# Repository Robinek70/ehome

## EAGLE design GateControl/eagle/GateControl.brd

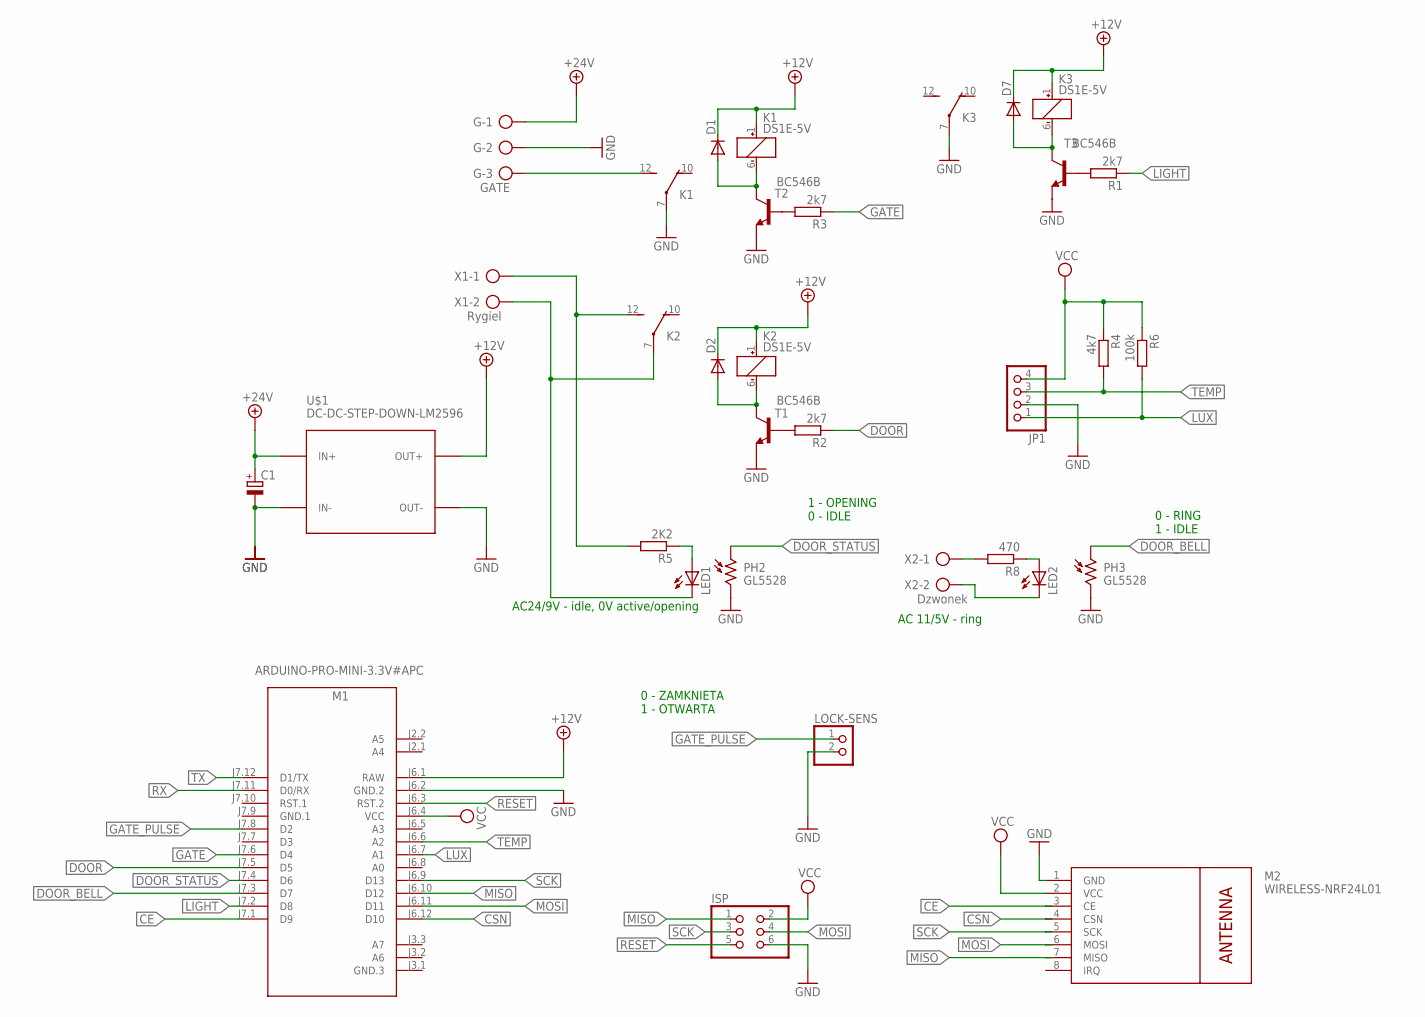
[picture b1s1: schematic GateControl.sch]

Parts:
C1: CPOL-EUE3.5-10; E3,5-10
D1, D2, D7: DIODE-C1702-05; C1702-05
G: GATE; AK500/3
ISP: PINHD-2X03_2.54; 2X03
JP1: PINHD-1X04_2.54; 1X04
K1, K2, K3: DS1E-5V; DS1E
LED1, LED2: LED5MM
LOCK-SENS: PINHD-1X02_2.54; 1X02
M1: ARDUINO-PRO-MINI-3.3V#APC; ARDUINO-PRO-MINI#APC
M2: WIRELESS-NRF24L01
PH2, PH3: GL5528; TO46-VT200
R1, R2, R3: 2k7; 0309V
R4: 4k7; 0309V
R5: 2K2; 0309V
R6: 100k; 0309V
R8: 470; 0309V
T1, T2, T3: BC546B; TO92-EBC
U$1: DC-DC-STEP-DOWN-LM2596
X1: Rygiel; AK500/2
X2: Dzwonek; AK500/2

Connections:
+12V: D1.C, D2.C, D7.C, K1.1 (+), K2.1 (+), K3.1 (+), M1.J6.1 (RAW), U$1.OUT+
+24V: C1.+, G.1, U$1.IN+
CE: M1.J7.1 (D9), M2.3 (CE)
CSN: M1.J6.12 (D10), M2.4 (CSN)
DOOR: M1.J7.5 (D5), R2.1
DOOR_BELL: M1.J7.3 (D7), PH3.1
DOOR_STATUS: M1.J7.4 (D6), PH2.1
GATE: M1.J7.6 (D4), R3.1
GATE_PULSE: LOCK-SENS.1, M1.J7.8 (D2)
GND: C1.-, G.2, ISP.6, JP1.2, K1.7, K3.7, LOCK-SENS.2, M1.J6.2 (GND.2), M2.1 (GND), PH2.2, PH3.2, T1.E, T2.E, T3.E, U$1.IN-, U$1.OUT-
GND.1: M1.J7.9 (GND.1)
LIGHT: M1.J7.2 (D8), R1.1
LUX: JP1.1, M1.J6.7 (A1), R6.2
MISO: ISP.1, M1.J6.10 (D12), M2.7 (MISO)
MOSI: ISP.4, M1.J6.11 (D11), M2.6 (MOSI)
unnamed: D7.A, K3.6 (-), T3.C
unnamed: R1.2, T3.B
unnamed: K2.12 (S), R5.2, X1.1
unnamed: K2.7, LED1.K (C), X1.2
unnamed: R2.2, T1.B
unnamed: D1.A, K1.6 (-), T2.C
unnamed: D2.A, K2.6 (-), T1.C
unnamed: R3.2, T2.B
unnamed: LED1.A, R5.1
unnamed: LED2.A, R8.1
unnamed: LED2.K (C), X2.2
unnamed: R8.2, X2.1
RESET: ISP.5, M1.J6.3 (RST.2)
RX: M1.J7.11 (D0/RX)
SCK: ISP.3, M1.J6.9 (D13), M2.5 (SCK)
TEMP: JP1.3, M1.J6.6 (A2), R4.2
TX: M1.J7.12 (D1/TX)
VCC: ISP.2, JP1.4, M1.J6.4 (VCC), M2.2 (VCC), R4.1, R6.1
VCC2: G.3, K1.12 (S)

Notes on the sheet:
AC24/9V - idle, 0V active/opening
AC 11/5V - ring
0 - RING 1 - IDLE
1 - OPENING 0 - IDLE
0 - ZAMKNIETA 1 - OTWARTA

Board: 2 copper layers, 30 parts (0 on the bottom side), 31 nets, no tracks yet.

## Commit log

2017-06-03 init
2017-06-03 INIT EAGLE
2017-08-22 added Sciemniacz / dimmer
2017-09-07 init GarageRepeater
2017-10-08 now use myRPlibs
2017-10-10 v 1.0 working fine
2018-02-10 v.3.08 fixes
2018-06-25 V_LIGHT_LEVEL -> V_LEVEL, to V_STATUS added DIM 100
2018-06-25 V_LIGHT_LEVEL -> V_LEVEL
2018-12-10 3.195R - reset on error fixes, on sending, power level
2019-01-18 3.22R multifunctional clicks/switch - long/click/double/triple
2019-02-08 3.26-200 - dimmer 50 steps, click fixes, 5x click reset, auto reset radio, switches parameter
2019-02-17 v.3.28 - resend switch value, reset fix

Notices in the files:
parts and their libraries:
diy-modules: Released under the Creative Commons Attribution 4.0 International License: http://creativecommons.org/licenses/by/4.0
